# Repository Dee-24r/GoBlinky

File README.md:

# My GoBlinky project

https://github.com/user-attachments/assets/78b2fccf-afea-48d7-8b8a-4e549cb79bda

This is a simple chaser board, sometimes called a blinky! Made all from scratch. What does she do? She Blinks!!

[Watch her in action](https://youtube.com/shorts/273GlsKtG_Y?si=tUAFjzuMFvb2yS4Z):
https://youtube.com/shorts/273GlsKtG_Y?si=tUAFjzuMFvb2yS4Z

[BOM](#bill-of-materials)

It's in the shape and design of a STOP sign, but it says "GO". Periodtt!
Bars are from my favourite spoken word artist, IBQuake :D

My schematic design:

My pcb:

3d view of my chaser board:

And the back:

## BILL OF MATERIALS

| Item                     | Cost   | Quantity | Description                  |
|--------------------------|--------|----------|------------------------------|
| Blinky Kit from Hack Club   | $15.00 | 1        | Kit for event                | https://stasis.hackclub.com/starter-projects/blinky |
| PCB (JLCPCB)             | $6.60  | 1        | Base of the blinky           |[Link](https://trade.jlcpcb.com/checkout) |
| Solder Iron with shipping costs           | $16.31  | 1        | Used to assemble the blinky  | [Link](http://amazon.com/gp/product/B098JD8HD3/ref=ewc_pr_img_1?smid=A19YGYI63H9AEE&th=1) |

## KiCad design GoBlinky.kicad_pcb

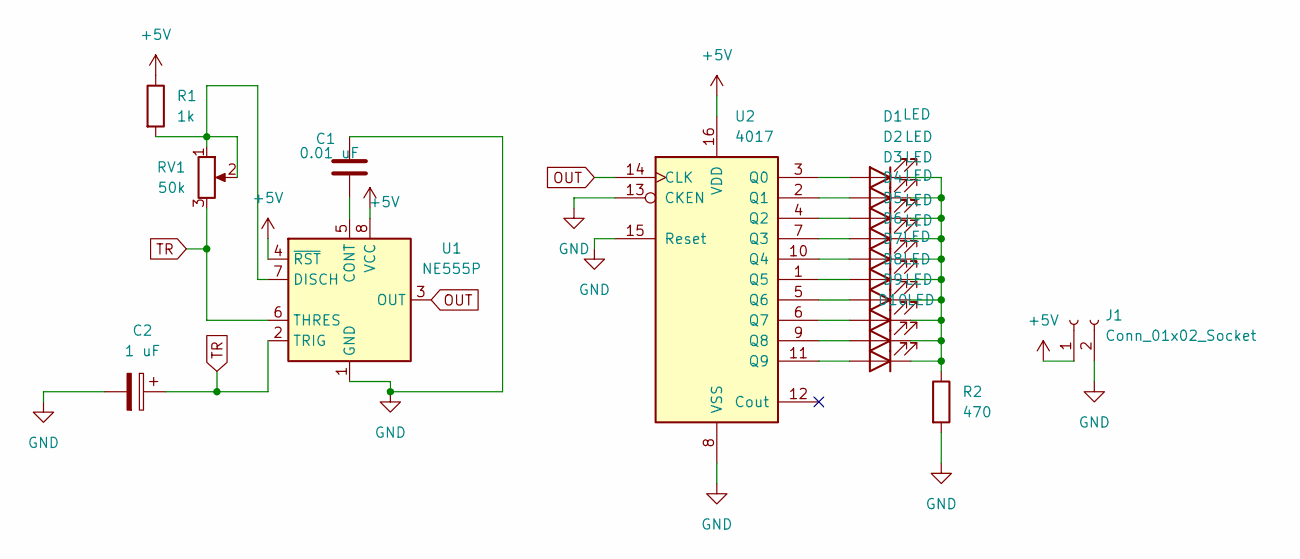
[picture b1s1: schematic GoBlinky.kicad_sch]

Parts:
C1: 0.01 uF; C_Disc_D7.5mm_W2.5mm_P5.00mm
C2: 1 uF; CP_Radial_D5.0mm_P2.00mm
D1, D2, D3, D4, D5, D6, D7, D8, D9, D10: LED; LED_D3.0mm
J1: Conn_01x02_Socket; PinHeader_1x02_P2.54mm_Vertical
R1: 1k; R_Axial_DIN0207_L6.3mm_D2.5mm_P7.62mm_Horizontal
R2: 470; R_Axial_DIN0207_L6.3mm_D2.5mm_P7.62mm_Horizontal
RV1: 50k; Potentiometer_Vishay_T93YA_Vertical
U1: NE555P; DIP-8_W7.62mm
U2: 4017; N16

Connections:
+5V: J1.1, R1.1, U1.4 (~RST), U1.8 (VCC), U2.16 (VDD)
GND: C1.2, C2.2, J1.2, R2.2, U1.1 (GND), U2.8 (VSS), U2.13 (CKEN), U2.15 (Reset)
unnamed: D1.2 (A), U2.3 (Q0)
unnamed: D1.1 (K), D2.1 (K), D3.1 (K), D4.1 (K), D5.1 (K), D6.1 (K), D7.1 (K), D8.1 (K), D9.1 (K), D10.1 (K), R2.1
unnamed: D2.2 (A), U2.2 (Q1)
unnamed: D3.2 (A), U2.4 (Q2)
unnamed: D4.2 (A), U2.7 (Q3)
unnamed: D5.2 (A), U2.10 (Q4)
unnamed: D6.2 (A), U2.1 (Q5)
unnamed: D7.2 (A), U2.5 (Q6)
unnamed: D8.2 (A), U2.6 (Q7)
unnamed: D9.2 (A), U2.9 (Q8)
unnamed: D10.2 (A), U2.11 (Q9)
unnamed: C1.1, U1.5 (CONT)
unnamed: R1.2, RV1.1, RV1.2, U1.7 (DISCH)
OUT: U1.3 (OUT), U2.14 (CLK)
TR: C2.1, RV1.3, U1.2 (TRIG), U1.6 (THRES)

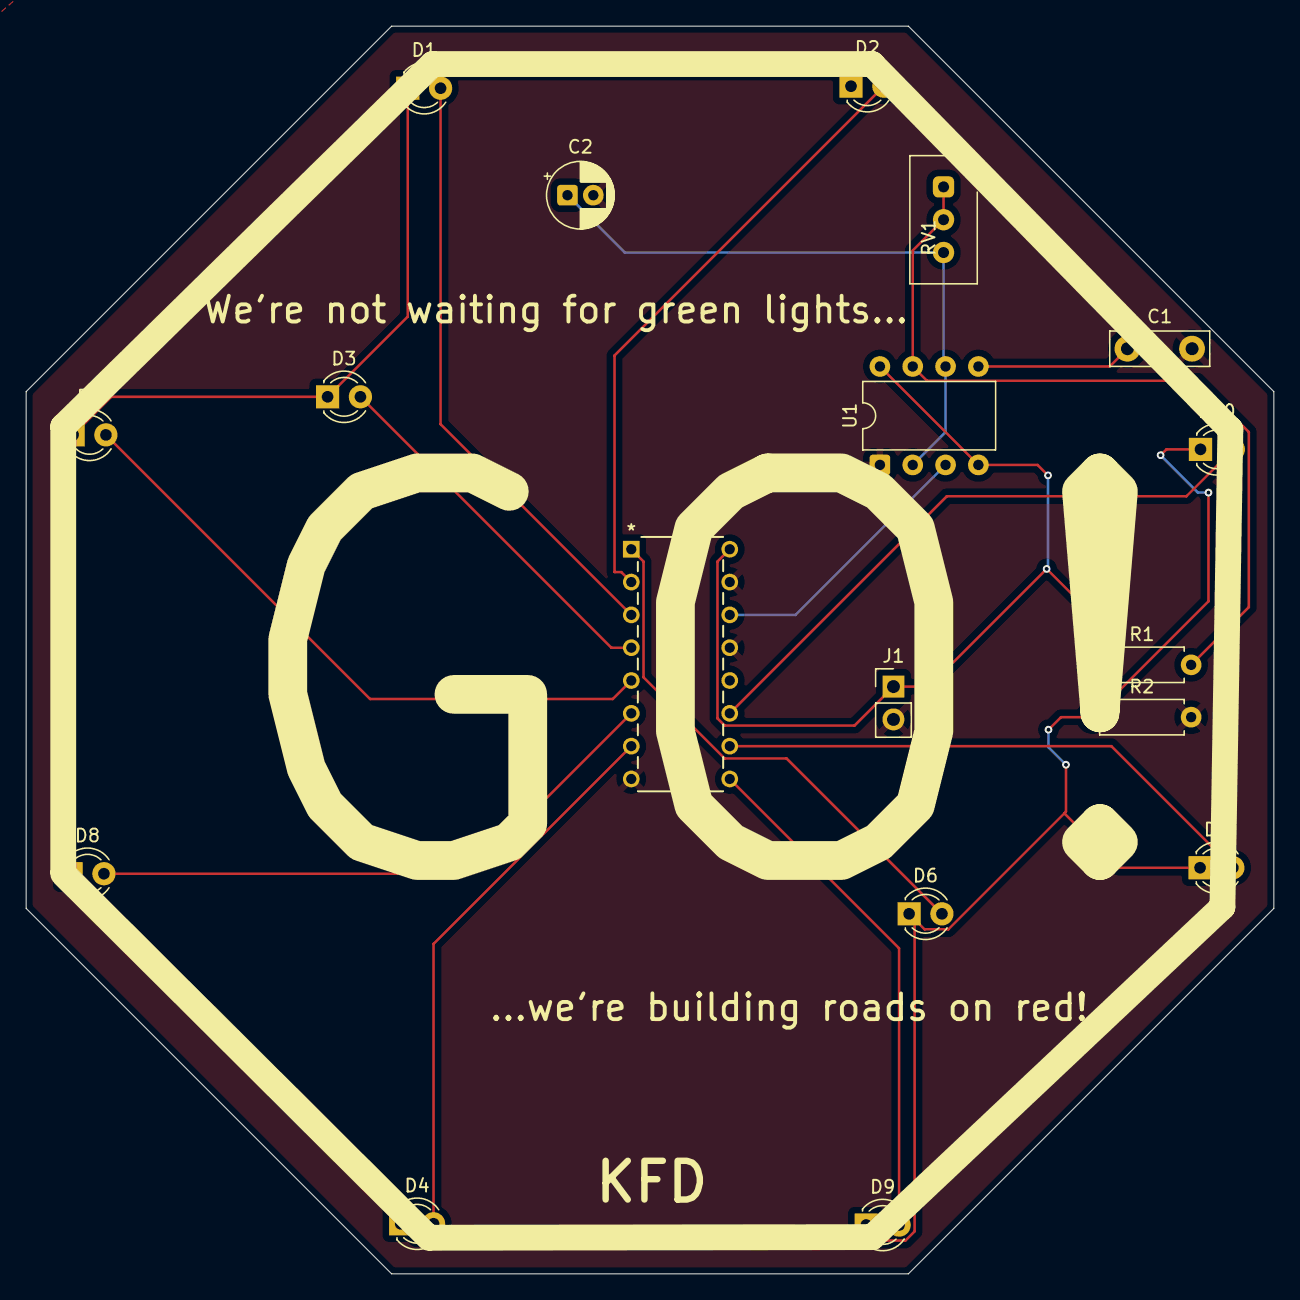
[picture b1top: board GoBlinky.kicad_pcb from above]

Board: 2 copper layers, 96.6 x 96.6 mm, 18 parts (0 on the bottom side), 17 nets.

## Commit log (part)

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2026-04-14 readme
2026-04-14 README updates
2026-04-14 gerbers
2026-04-14 resetting images
2026-04-14 image reset again
2026-04-14 sentence edit
2026-04-14 more images
2026-04-14 link
